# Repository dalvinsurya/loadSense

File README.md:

# loadSense
LGT8F328P Based Strain Gauge Levelling Sensor For 3D Printers

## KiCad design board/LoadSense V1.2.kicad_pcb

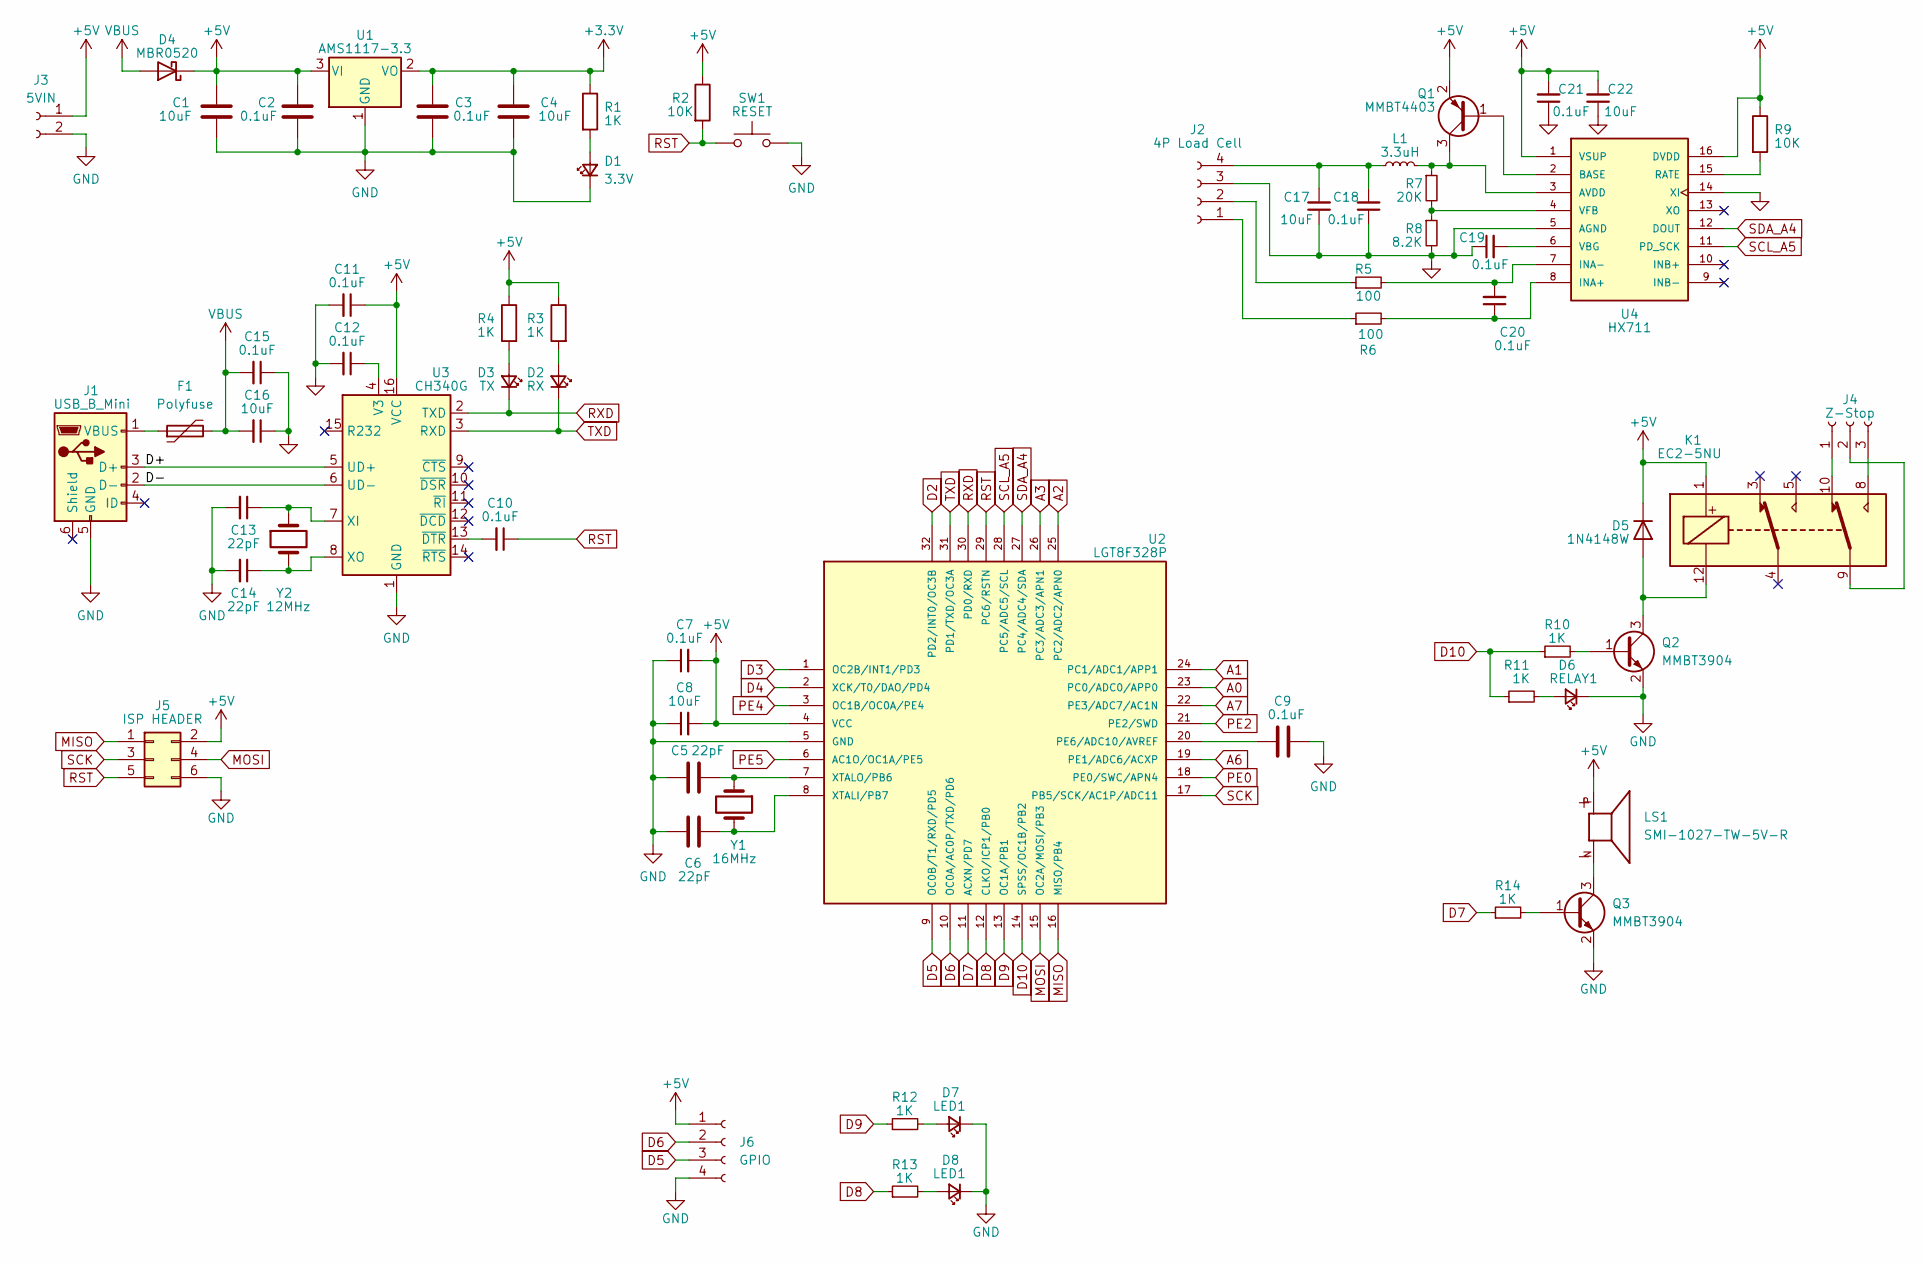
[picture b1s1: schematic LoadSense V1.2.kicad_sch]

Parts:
C1, C4, C8, C16, C17, C22: 10uF; C_0603_1608Metric_Pad1.08x0.95mm_HandSolder
C2, C3, C7, C9, C10, C11, C12, C15, C18, C19, C20, C21: 0.1uF; C_0603_1608Metric_Pad1.08x0.95mm_HandSolder
C5, C6, C13, C14: 22pF; C_0603_1608Metric_Pad1.08x0.95mm_HandSolder
D1: 3.3V; LED_0805_2012Metric_Pad1.15x1.40mm_HandSolder
D2: RX; LED_0805_2012Metric_Pad1.15x1.40mm_HandSolder
D3: TX; LED_0805_2012Metric_Pad1.15x1.40mm_HandSolder
D4: MBR0520; D_SOD-123
D5: 1N4148W; D_SOD-123
D6: RELAY1; LED_0805_2012Metric_Pad1.15x1.40mm_HandSolder
D7, D8: LED1; LED_0805_2012Metric_Pad1.15x1.40mm_HandSolder
F1: Polyfuse; Fuse_1812_4532Metric_Pad1.30x3.40mm_HandSolder
J1: USB_B_Mini; USB_Mini-B_Tensility_54-00023_Vertical
J2: 4P Load Cell; JST_PH_B4B-PH-K_1x04_P2.00mm_Vertical
J3: 5VIN; JST_PH_B2B-PH-K_1x02_P2.00mm_Vertical
J4: Z-Stop; JST_PH_B3B-PH-K_1x03_P2.00mm_Vertical
J5: ISP HEADER; PinHeader_2x03_P2.54mm_Vertical
J6: GPIO; JST_PH_B4B-PH-K_1x04_P2.00mm_Vertical
K1: EC2-5NU; Relay_DPDT_Kemet_EC2
L1: 3.3uH; L_0603_1608Metric_Pad1.05x0.95mm_HandSolder
LS1: SMI-1027-TW-5V-R; PUI_SMI-1027-TW-5V-R; PARTREV 11/11/2014
Q1: MMBT4403; SOT-23
Q2, Q3: MMBT3904; SOT-23
R1, R3, R4, R10, R11, R12, R13, R14: 1K; R_0603_1608Metric_Pad0.98x0.95mm_HandSolder
R2, R9: 10K; R_0603_1608Metric_Pad0.98x0.95mm_HandSolder
R5, R6: 100; R_0603_1608Metric_Pad0.98x0.95mm_HandSolder
R7: 20K; R_0603_1608Metric_Pad0.98x0.95mm_HandSolder
R8: 8.2K; R_0603_1608Metric_Pad0.98x0.95mm_HandSolder
SW1: RESET; SW_SPST_CK_RS282G05A3
U1: AMS1117-3.3; SOT-223-3_TabPin2
U2: LGT8F328P; TQFP-32_7x7mm_P0.8mm
U3: CH340G; SOIC-16_3.9x9.9mm_P1.27mm
U4: HX711; SOP127P600X180-16N; PARTREV V2.0
Y1: 16MHz; Crystal_SMD_HC49-SD
Y2: 12MHz; Crystal_SMD_HC49-SD

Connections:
+3.3V: C3.1, C4.1, R1.1, U1.2 (VO)
+5V: C1.1, C2.1, C7.2, C8.2, C11.1, C21.2, C22.2, D4.1 (K), D5.1 (K), J3.1, J5.2, J6.1, K1.1, LS1.P, Q1.2 (E), R2.1, R3.1, R4.1, R9.1, U1.3 (VI), U2.4 (VCC), U3.16 (VCC), U4.1 (VSUP), U4.16 (DVDD)
/D+: J1.3 (D+), U3.5 (UD+)
/D-: J1.2 (D-), U3.6 (UD-)
A0: U2.23 (PC0/ADC0/APP0)
A1: U2.24 (PC1/ADC1/APP1)
A2: U2.25 (PC2/ADC2/APN0)
A3: U2.26 (PC3/ADC3/APN1)
A6: U2.19 (PE1/ADC6/ACXP)
A7: U2.22 (PE3/ADC7/AC1N)
D2: U2.32 (PD2/INT0/OC3B)
D3: U2.1 (OC2B/INT1/PD3)
D4: U2.2 (XCK/T0/DAO/PD4)
D5: J6.3, U2.9 (OC0B/T1/RXD/PD5)
D6: J6.2, U2.10 (OC0A/AC0P/TXD/PD6)
D7: R14.1, U2.11 (ACXN/PD7)
D8: R13.1, U2.12 (CLKO/ICP1/PB0)
D9: R12.1, U2.13 (OC1A/PB1)
D10: R10.1, R11.1, U2.14 (SPSS/OC1B/PB2)
GND: C1.2, C2.2, C3.2, C4.2, C5.1, C6.1, C7.1, C8.1, C9.2, C11.2, C12.2, C13.2, C14.2, C15.1, C16.1, C17.1, C18.1, C19.1, C21.1, C22.1, D1.1 (K), D6.1 (K), D7.1 (K), D8.1 (K), J1.5 (GND), J2.3, J3.2, J5.6, J6.4, Q2.2 (E), Q3.2 (E), R8.2, SW1.2, U1.1 (GND), U2.5 (GND), U3.1 (GND), U4.5 (AGND), U4.14 (XI)
MISO: J5.1, U2.16 (MISO/PB4)
MOSI: J5.4, U2.15 (OC2A/MOSI/PB3)
unnamed: C5.2, U2.7 (XTALO/PB6), Y1.1
unnamed: C6.2, U2.8 (XTALI/PB7), Y1.2
unnamed: C9.1, U2.20 (PE6/ADC10/AVREF)
unnamed: C10.2, U3.13 (~DTR)
unnamed: C12.1, U3.4 (V3)
unnamed: C13.1, U3.7 (XI), Y2.1
unnamed: C14.1, U3.8 (XO), Y2.2
unnamed: C17.2, C18.2, J2.4, L1.1
unnamed: C19.2, U4.6 (VBG)
unnamed: C20.1, R6.2, U4.8 (INA+)
unnamed: C20.2, R5.2, U4.7 (INA-)
unnamed: D1.2 (A), R1.2
unnamed: D2.2 (A), R3.2
unnamed: D3.2 (A), R4.2
unnamed: D5.2 (A), K1.12, Q2.3 (C)
unnamed: D6.2 (A), R11.2
unnamed: D7.2 (A), R12.2
unnamed: D8.2 (A), R13.2
unnamed: F1.1, J1.1 (VBUS)
unnamed: J2.1, R6.1
unnamed: J2.2, R5.1
unnamed: J4.1, K1.10
unnamed: J4.2, K1.9
unnamed: J4.3, K1.8
unnamed: L1.2, Q1.3 (C), R7.1, U4.3 (AVDD)
unnamed: LS1.N, Q3.3 (C)
unnamed: Q1.1 (B), U4.2 (BASE)
unnamed: Q2.1 (B), R10.2
unnamed: Q3.1 (B), R14.2
unnamed: R7.2, R8.1, U4.4 (VFB)
unnamed: R9.2, U4.15 (RATE)
PE0: U2.18 (PE0/SWC/APN4)
PE2: U2.21 (PE2/SWD)
PE4: U2.3 (OC1B/OC0A/PE4)
PE5: U2.6 (AC1O/OC1A/PE5)
RST: C10.1, J5.5, R2.2, SW1.1, U2.29 (PC6/RSTN)
RXD: D3.1 (K), U2.30 (PD0/RXD), U3.2 (TXD)
SCK: J5.3, U2.17 (PB5/SCK/AC1P/ADC11)
SCL_A5: U2.28 (PC5/ADC5/SCL), U4.11 (PD_SCK)
SDA_A4: U2.27 (PC4/ADC4/SDA), U4.12 (DOUT)
TXD: D2.1 (K), U2.31 (PD1/TXD/OC3A), U3.3 (RXD)
VBUS: C15.2, C16.2, D4.2 (A), F1.2

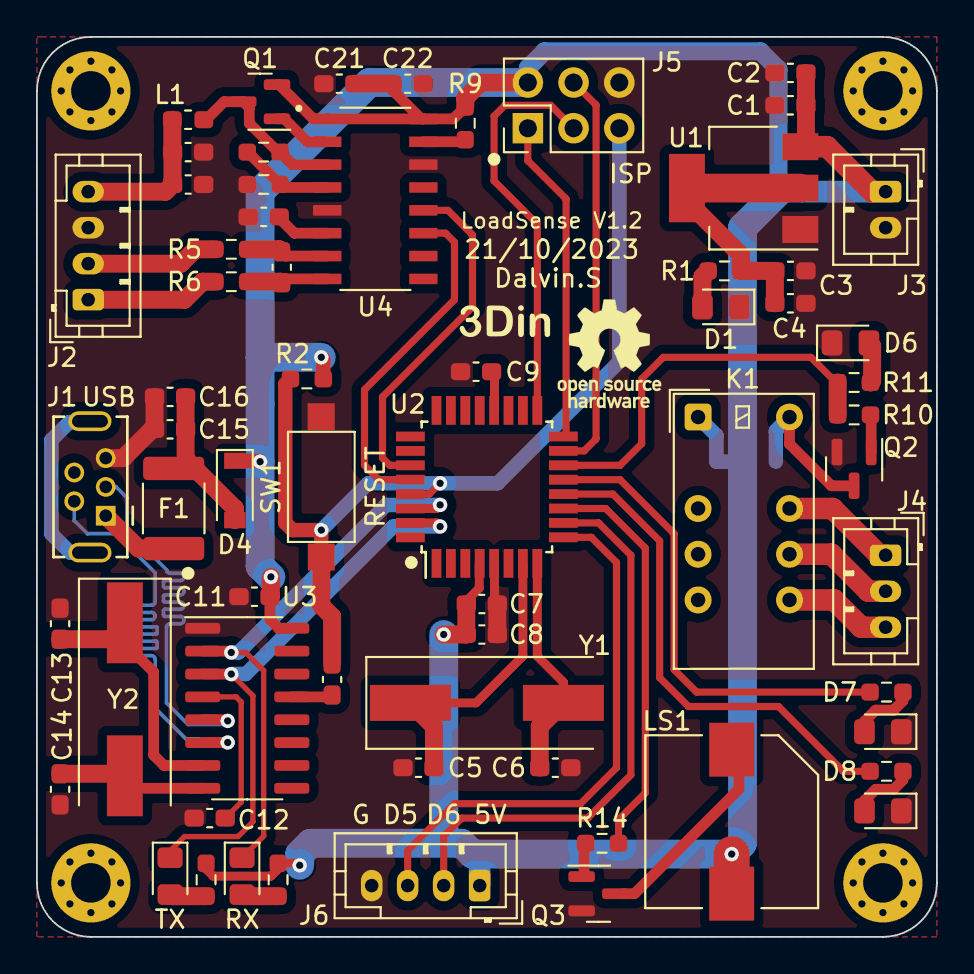
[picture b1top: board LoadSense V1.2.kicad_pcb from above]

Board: 2 copper layers, 50.0 x 50.0 mm, 64 parts (1 on the bottom side), 51 nets.

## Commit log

2023-10-22 Create folder board
